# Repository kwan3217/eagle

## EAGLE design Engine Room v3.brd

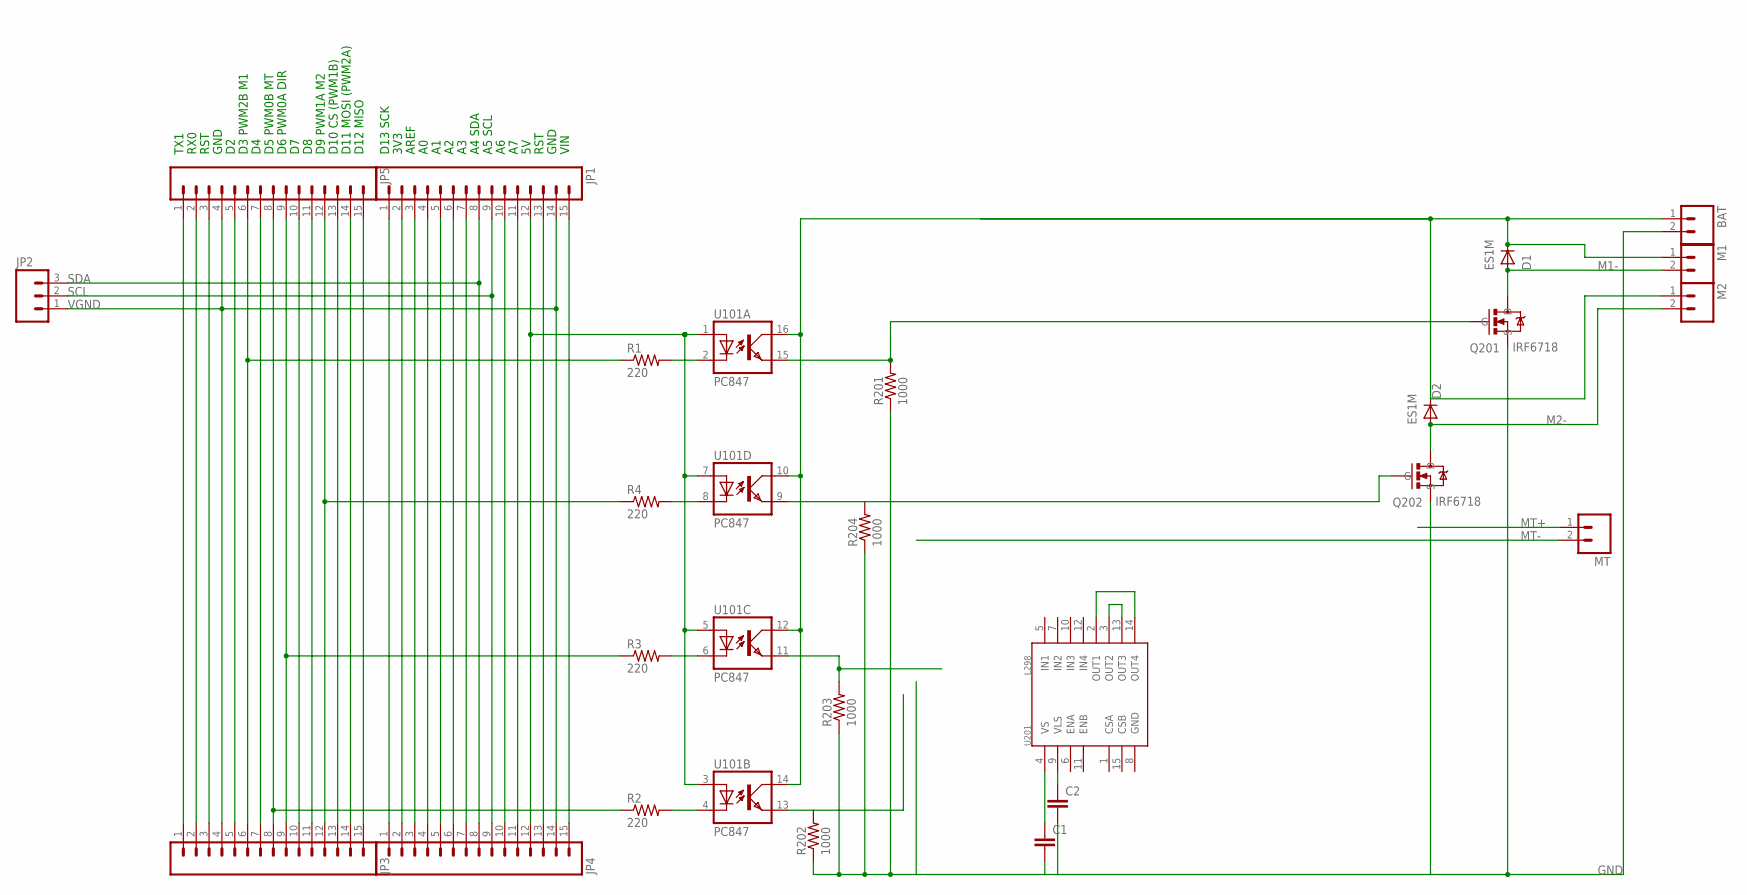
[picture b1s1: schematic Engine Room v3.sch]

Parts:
BAT: M02PTH4; 1X02_XTRA_BIG
C1, C2: CAP0402-CAP; 0402-CAP
D1, D2: ES1M; DO-214AC
JP1, JP5: M15LOCK; 1X15_LOCK
JP2: M03LOCK; 1X03_LOCK
JP3, JP4: M15; 1X15
M1, M2: M02PTH4; 1X02_XTRA_BIG
MT: M02PTH; 1X02
Q201, Q202: IRF6718; DIRECTFET_L6
R1, R2, R3, R4: 220; 0402-RES
R201, R202, R203, R204: 1000; 0402-RES
U101: PC847; DIL16
U201: L298; MULTIWATT15

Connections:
GND: BAT.2, C1.2, C2.2, Q201.S, Q202.S, R201.1, R202.1, R203.1, R204.1
IN1: JP3.6, JP5.6, R1.1
IN2: JP3.12, JP5.12, R4.1
IN3: JP3.8, JP5.8, R2.1
M1-: D1.A, M1.2, Q201.D1 (D), Q201.D2 (D)
M2-: D2.A, M2.2, Q202.D1 (D), Q202.D2 (D)
MT+: MT.1
MT-: MT.2
unnamed: R4.2, U101.8 (C)
unnamed: R3.2, U101.6 (C)
unnamed: R1.2, U101.2 (C)
unnamed: R2.2, U101.4 (C)
unnamed: JP1.15, JP4.15
unnamed: Q201.G, R201.2, U101.15 (EMIT)
unnamed: U201.2 (OUT1), U201.14 (OUT4)
unnamed: Q202.G, R204.2, U101.9 (EMIT)
unnamed: U201.3 (OUT2), U201.13 (OUT3)
unnamed: R203.2, U101.11 (EMIT)
unnamed: JP3.9, JP5.9, R3.1
unnamed: JP3.1, JP5.1
unnamed: JP3.2, JP5.2
unnamed: JP3.3, JP5.3
unnamed: R202.2, U101.13 (EMIT)
unnamed: C2.1, U201.9 (VLS)
unnamed: C1.1, U201.4 (VS)
unnamed: JP3.5, JP5.5
unnamed: JP3.15, JP5.15
unnamed: JP3.14, JP5.14
unnamed: JP3.13, JP5.13
unnamed: JP3.7, JP5.7
unnamed: JP3.10, JP5.10
unnamed: JP3.11, JP5.11
unnamed: JP1.13, JP4.13
unnamed: JP1.11, JP4.11
unnamed: JP1.10, JP4.10
unnamed: JP1.7, JP4.7
unnamed: JP1.6, JP4.6
unnamed: JP1.5, JP4.5
unnamed: JP1.4, JP4.4
unnamed: JP1.3, JP4.3
unnamed: JP1.2, JP4.2
unnamed: JP1.1, JP4.1
SCL: JP1.9, JP2.2, JP4.9
SDA: JP1.8, JP2.3, JP4.8
VCC: JP1.12, JP4.12, U101.1 (A), U101.3 (A), U101.5 (A), U101.7 (A)
VDD: BAT.1, D1.C, D2.C, M1.1, M2.1, U101.10 (COL), U101.12 (COL), U101.14 (COL), U101.16 (COL)
VGND: JP1.14, JP2.1, JP3.4, JP4.14, JP5.4

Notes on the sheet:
VIN
GND
RST
A5 SCL
A4 SDA
AREF
3V3
D13 SCK
D12 MISO
D11 MOSI (PWM2A)
D10 CS (PWM1B)
D9 PWM1A M2
D6 PWM0A DIR
D5 PWM0B MT
D3 PWM2B M1
RX0
TX1

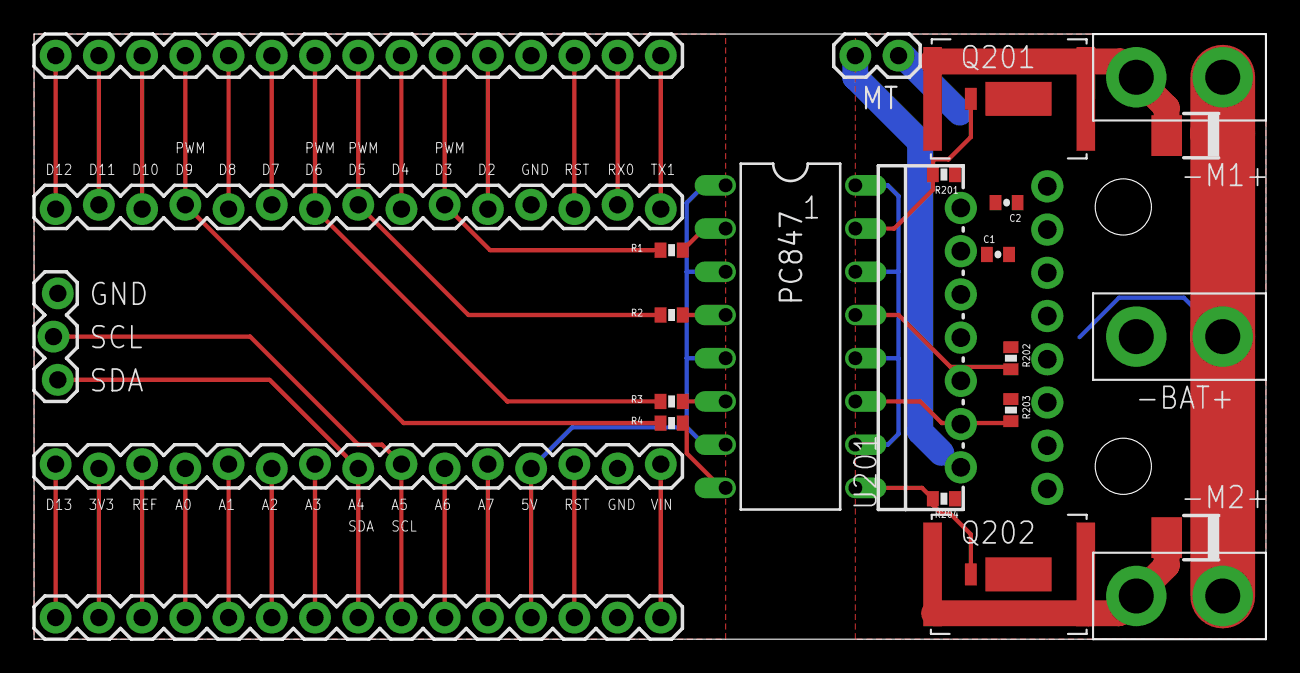
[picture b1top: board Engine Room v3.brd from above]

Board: 2 copper layers, 72.4 x 35.6 mm, 28 parts (1 on the bottom side), 45 nets.

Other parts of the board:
U$1, U$2: STAND-OFF
U$3: KWAN_CIRCLE

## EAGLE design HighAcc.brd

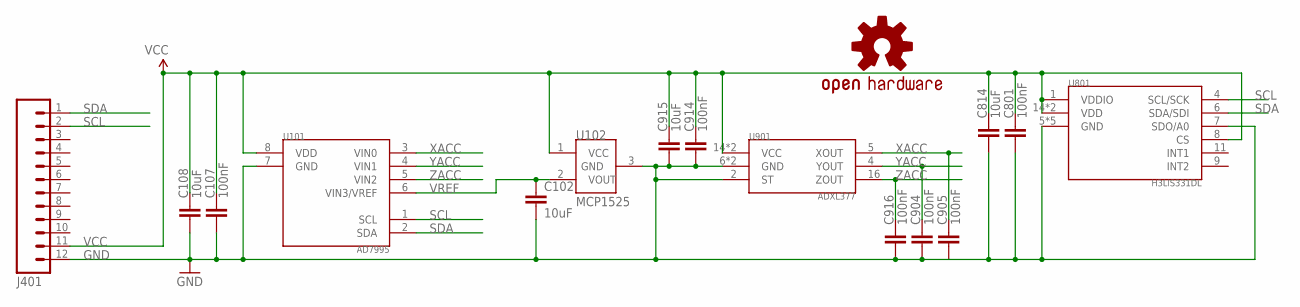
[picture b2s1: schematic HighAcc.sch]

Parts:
C102, C108, C814, C915: 10uF; 0603-CAP; DIGIKEY 445-7486-1-ND
C107, C801, C904, C905, C914, C916: 100nF; 0603-CAP; DIGIKEY 445-1316-1-ND
J401: M12PTH; 1X12; DIGIKEY $NOPART
U101: AD7995; SOT-23-8
U102: MCP1525; SOT-23-3
U801: H3LIS331DL; LLGA16
U901: ADXL377
U$2: OSHW-LOGOS; OSHW-LOGO-S; DIGIKEY $NOPART

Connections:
GND: C102.2, C107.2, C108.2, C801.2, C814.2, C904.2, C905.2, C914.2, C915.2, C916.2, J401.12, U101.7 (GND), U102.3 (GND), U801.5 (GND), U801.7 (SDO/A0), U801.10 (GND), U801.12 (GND), U801.13 (GND), U801.16 (GND), U901.2 (ST), U901.6 (GND), U901.7 (GND)
SCL: J401.2, U101.1 (SCL), U801.4 (SCL/SCK)
SDA: J401.1, U101.2 (SDA), U801.6 (SDA/SDI)
VCC: C107.1, C108.1, C801.1, C814.1, C914.1, C915.1, J401.11, U101.8 (VDD), U102.1 (VCC), U801.1 (VDDIO), U801.8 (CS), U801.14 (VDD), U801.15 (VDD), U901.14 (VCC), U901.15 (VCC)
VREF: C102.1, U101.6 (VIN3/VREF), U102.2 (VOUT)
XACC: C905.1, U101.3 (VIN0), U901.5 (XOUT)
YACC: C904.1, U101.4 (VIN1), U901.4 (YOUT)
ZACC: C916.1, U101.5 (VIN2), U901.16 (ZOUT)

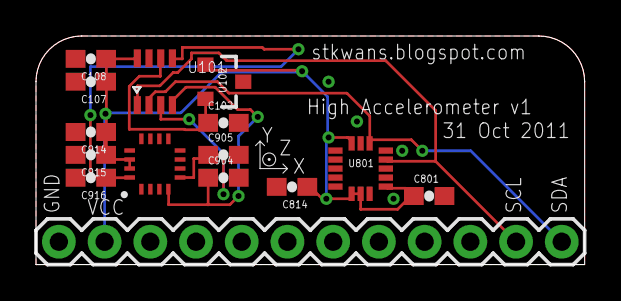
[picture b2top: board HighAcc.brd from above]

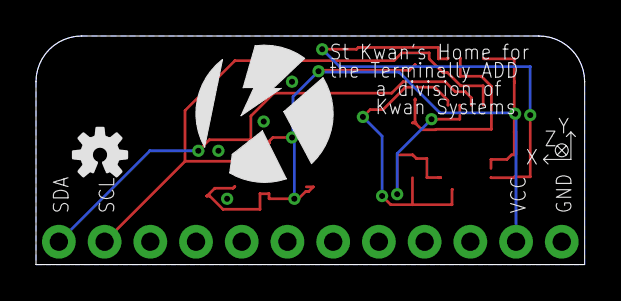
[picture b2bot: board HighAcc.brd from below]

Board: 2 copper layers, 30.5 x 12.7 mm, 17 parts (2 on the bottom side), 8 nets.

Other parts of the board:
U$1: KWAN_CIRCLE

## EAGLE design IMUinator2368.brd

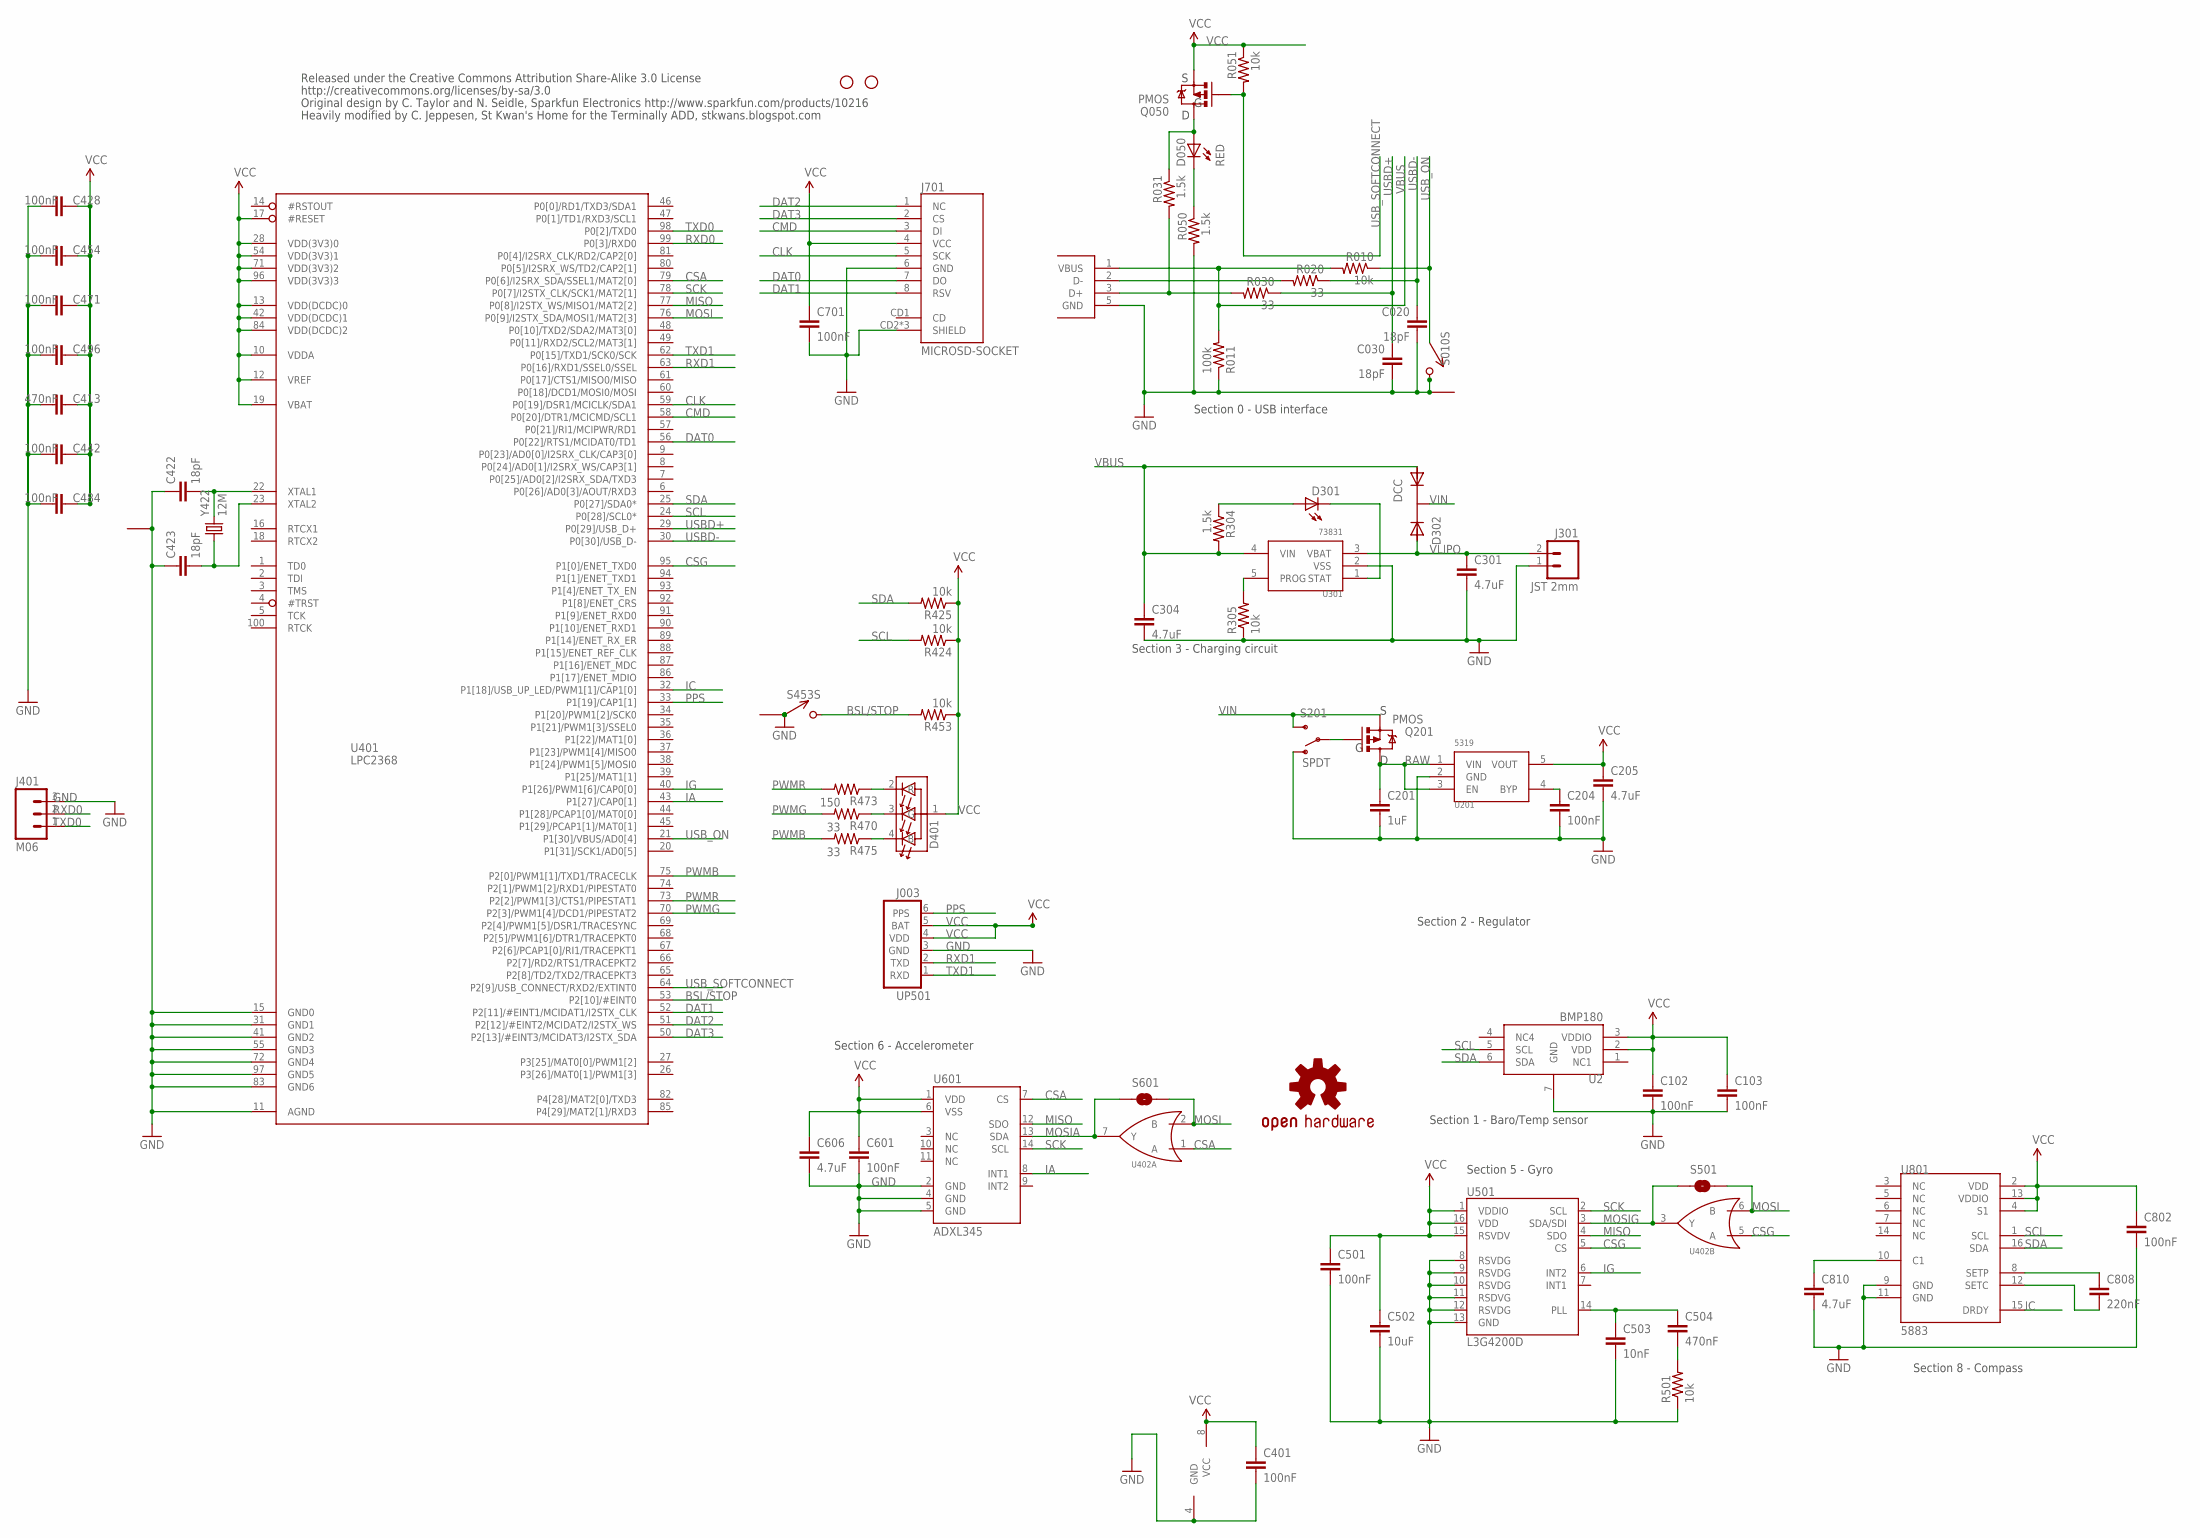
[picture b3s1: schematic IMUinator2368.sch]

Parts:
C020, C030, C422, C423: 18pF; 0402-CAP; DIGIKEY 445-1238-1-ND
C102, C103, C204, C401, C428, C442, C454, C471, C484, C496, C501, C601, C701, C802: 100nF; 0402-CAP; DIGIKEY 445-1268-1-ND
C201: 1uF; 0402-CAP; DIGIKEY 445-1415-1-ND
C205, C301, C304, C606, C810: 4.7uF; 0402-CAP; DIGIKEY 445-7395-1-ND
C413, C504: 470nF; 0402-CAP; DIGIKEY 445-4976-1-ND
C502: 10uF; 0603-CAP; DIGIKEY 445-7486-1-ND
C503: 10nF; 0402-CAP; DIGIKEY 445-4943-1-ND
C808: 220nF; 0402-CAP; DIGIKEY 445-4972-1-ND
D050, D301: RED; LED-0603; DIGIKEY 350-2029-1-ND
D302: DCC; SOT-23-3; DIGIKEY 568-6500-1-ND
D401: RGB; HSMF-C118; DIGIKEY 516-1778-1-ND
J001: USB_MICROB_JST; UB-MC5BR3-SD204-4S; DIGIKEY 455-2562-1-ND
J003: UP501; DIGIKEY $NOPART
J301: JST 2mm; JST-2-SMD; DIGIKEY 455-1749-1-ND
J401: M06; 1X03; DIGIKEY $NOPART
J701: MICROSD-SOCKET; MICROSD-SOCKET-PP; DIGIKEY 101-00581-59-1-ND
JP1, JP2: STAND-OFF; DIGIKEY $NOPART
Q050, Q201: PMOS; SOT23-3; DIGIKEY NTR1P02T1GOSCT-ND
R010, R051, R305, R424, R425, R453, R501: 10k; 0402-RES; DIGIKEY P10.0KLCT-ND
R011: 100k; 0402-RES; DIGIKEY P100KLCT-ND
R020, R030, R475: 33; 0402-RES; DIGIKEY P33.0LCT-ND
R031, R050, R304: 1.5k; 0402-RES; DIGIKEY P1.50KLCT-ND
R470: 33; 0402-RES; DIGIKEY P150LCT-ND
R473: 150; 0402-RES; DIGIKEY P33.0LCT-ND
S010, S453: SPST; B3U-1100P; DIGIKEY SW1021CT-ND
S201: SPDT; AYZ0202; DIGIKEY 401-2013-1-ND
S501, S601: SOLDERJUMPERNO; SJ_2S-NO; DIGIKEY $NOPART
U2: BMP180; DIGIKEY 828-1027-1-ND
U201: 5319; SOT-23-5; DIGIKEY 576-1910-1-ND
U301: 73831; SOT-23-5; DIGIKEY MCP73831T-2ACI/OTCT-ND
U401: LPC2368; LQFP100; DIGIKEY 568-3997-ND
U402: 7432; DCU_8; DIGIKEY 296-13268-1-ND
U501: L3G4200D; LGA16-4X4; DIGIKEY 497-11071-1-ND
U601: ADXL345; LGA14; DIGIKEY ADXL345BCCZ-RL7CT-ND
U801: 5883; 16LPCC; DIGIKEY 342-1082-1-ND
U$3: OSHW-LOGOS; OSHW-LOGO-S; DIGIKEY $NOPART
Y422: 12M; CRYSTAL_SMD; DIGIKEY 887-1316-1-ND

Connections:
BSL/STOP: R453.2, S453.P$2 (2), U401.53 (P2[10]/#EINT0)
CLK: J701.5 (SCK), U401.59 (P0[19]/DSR1/MCICLK/SDA1)
CMD: J701.3 (DI), U401.58 (P0[20]/DTR1/MCICMD/SCL1)
CONN_D+: J001.3 (D+), R030.2, R031.2
CONN_D-: J001.2 (D-), R020.2
CSA: U401.79 (P0[6]/I2SRX_SDA/SSEL1/MAT2[0]), U402.1 (A), U601.7 (CS)
CSG: U401.95 (P1[0]/ENET_TXD0), U402.5 (A), U501.5 (CS)
DAT0: J701.7 (DO), U401.56 (P0[22]/RTS1/MCIDAT0/TD1)
DAT1: J701.8 (RSV), U401.52 (P2[11]/#EINT1/MCIDAT1/I2STX_CLK)
DAT2: J701.1 (NC), U401.51 (P2[12]/#EINT2/MCIDAT2/I2STX_WS)
DAT3: J701.2 (CS), U401.50 (P2[13]/#EINT3/MCIDAT3/I2STX_SDA)
DB: D401.4 (B), R475.1
DG: D401.2 (R), R473.1
DR: D401.3 (G), R470.1
GND: C020.2, C030.2, C102.2, C103.2, C201.2, C204.2, C205.2, C301.2, C304.2, C401.2, C413.2, C422.1, C423.1, C428.2, C442.2, C454.2, C471.2, C484.2, C496.2, C501.2, C502.2, C503.2, C601.2, C606.2, C701.2, C802.2, C810.2, J001.5 (GND), J003.3 (GND), J301.1, J401.3, J701.6 (GND), J701.CD2 (SHIELD), J701.GND1 (SHIELD), J701.GND3 (SHIELD), R011.1, R050.2, R305.1, R501.1, S010.P$2 (2), S010.P$3 (1), S201.1 (O), S453.P$1 (1), S453.P$3 (1), U2.7 (GND), U201.2 (GND), U301.2 (VSS), U401.11 (AGND), U401.15 (GND0), U401.31 (GND1), U401.41 (GND2), U401.55 (GND3), U401.72 (GND4), U401.83 (GND6), U401.97 (GND5), U402.4 (GND), U501.8 (RSVDG), U501.9 (RSVDG), U501.10 (RSVDG), U501.11 (RSDVG), U501.12 (RSVDG), U501.13 (GND), U601.2 (GND), U601.4 (GND), U601.5 (GND), U801.9 (GND), U801.11 (GND), Y422.2 (1)
IA: U401.43 (P1[27]/CAP0[1]), U601.8 (INT1)
IC: U401.32 (P1[18]/USB_UP_LED/PWM1[1]/CAP1[0]), U801.15 (DRDY)
IG: U401.40 (P1[26]/PWM1[6]/CAP0[0]), U501.6 (INT2)
MISO: U401.77 (P0[8]/I2STX_WS/MISO1/MAT2[2]), U501.4 (SDO), U601.12 (SDO)
MOSI: S501.2, S601.2, U401.76 (P0[9]/I2STX_SDA/MOSI1/MAT2[3]), U402.2 (B), U402.6 (B)
MOSIA: S601.1, U402.7 (Y), U601.13 (SDA)
MOSIG: S501.1, U402.3 (Y), U501.3 (SDA/SDI)
unnamed: D301.A, R304.1
unnamed: C503.1, C504.1, U501.14 (PLL)
unnamed: C504.2, R501.2
unnamed: D050.A, Q050.3 (D), R031.1
unnamed: D050.C, R050.1
unnamed: C808.1, U801.8 (SETP)
unnamed: C808.2, U801.12 (SETC)
unnamed: C810.1, U801.10 (C1)
unnamed: C204.1, U201.4 (BYP)
PPS: J003.6 (PPS), U401.33 (P1[19]/CAP1[1])
PWMB: R475.2, U401.75 (P2[0]/PWM1[1]/TXD1/TRACECLK)
PWMG: R470.2, U401.70 (P2[3]/PWM1[4]/DCD1/PIPESTAT2)
PWMR: R473.2, U401.73 (P2[2]/PWM1[3]/CTS1/PIPESTAT1)
PWR_SWITCH: Q201.1 (G), S201.2
RAW: C201.1, Q201.3 (D), U201.1 (VIN), U201.3 (EN)
REG_PROG: R305.2, U301.5 (PROG)
REG_STAT: D301.C, U301.1 (STAT)
RXD0: J401.2, U401.99 (P0[3]/RXD0)
RXD1: J003.2 (TXD), U401.63 (P0[16]/RXD1/SSEL0/SSEL)
SCK: U401.78 (P0[7]/I2STX_CLK/SCK1/MAT2[1]), U501.2 (SCL), U601.14 (SCL)
SCL: R424.2, U2.5 (SCL), U401.24 (P0[28]/SCL0*), U801.1 (SCL)
SDA: R425.2, U2.6 (SDA), U401.25 (P0[27]/SDA0*), U801.16 (SDA)
TXD0: J401.1, U401.98 (P0[2]/TXD0)
TXD1: J003.1 (RXD), U401.62 (P0[15]/TXD1/SCK0/SCK)
USBD+: C030.1, R030.1, U401.29 (P0[29]/USB_D+)
USBD-: C020.1, R020.1, U401.30 (P0[30]/USB_D-)
USB_ON: R010.1, S010.P$1 (1), U401.21 (P1[30]/VBUS/AD0[4])
USB_SOFTCONNECT: Q050.1 (G), R051.2, U401.64 (P2[9]/USB_CONNECT/RXD2/EXTINT0)
VBUS: C304.1, D302.1 (A1), J001.1 (VBUS), R010.2, R011.2, R304.2, U301.4 (VIN)
VCC: C102.1, C103.1, C205.1, C401.1, C413.1, C428.1, C442.1, C454.1, C471.1, C484.1, C496.1, C501.1, C502.1, C601.1, C606.1, C701.1, C802.1, D401.1 (A), J003.4 (VDD), J003.5 (BAT), J701.4 (VCC), Q050.2 (S), R051.1, R424.1, R425.1, R453.1, U2.2 (VDD), U2.3 (VDDIO), U201.5 (VOUT), U401.10 (VDDA), U401.12 (VREF), U401.13 (VDD(DCDC)0), U401.17 (#RESET), U401.19 (VBAT), U401.28 (VDD(3V3)0), U401.42 (VDD(DCDC)1), U401.54 (VDD(3V3)1), U401.71 (VDD(3V3)2), U401.84 (VDD(DCDC)2), U401.96 (VDD(3V3)3), U402.8 (VCC), U501.1 (VDDIO), U501.15 (RSVDV), U501.16 (VDD), U601.1 (VDD), U601.6 (VSS), U801.2 (VDD), U801.4 (S1), U801.13 (VDDIO)
VIN: D302.3 (K), Q201.2 (S), S201.3 (S)
VLIPO: C301.1, D302.2 (A2), J301.2, U301.3 (VBAT)
XTAL1: C422.2, U401.22 (XTAL1), Y422.3 (2)
XTAL2: C423.2, U401.23 (XTAL2), Y422.1

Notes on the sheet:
Section 2 - Regulator
Section 3 - Charging circuit
Section 0 - USB interface
Released under the Creative Commons Attribution Share-Alike 3.0 License
http://creativecommons.org/licenses/by-sa/3.0
Original design by C. Taylor and N. Seidle, Sparkfun Electronics http://www.sparkfun.com/products/10216
Heavily modified by C. Jeppesen, St Kwan's Home for the Terminally ADD, stkwans.blogspot.com
Section 5 - Gyro
Section 6 - Accelerometer
Section 1 - Baro/Temp sensor
Section 8 - Compass

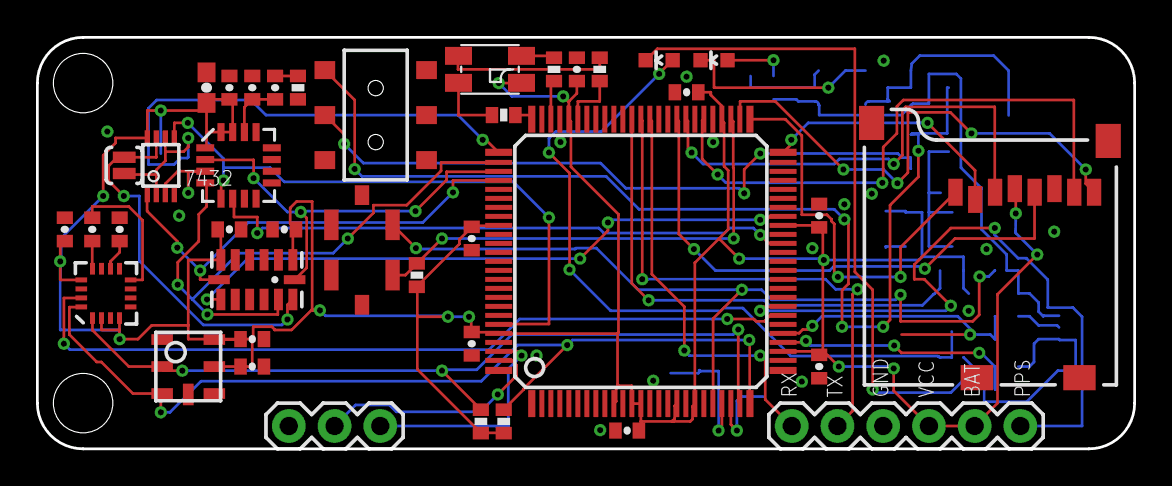
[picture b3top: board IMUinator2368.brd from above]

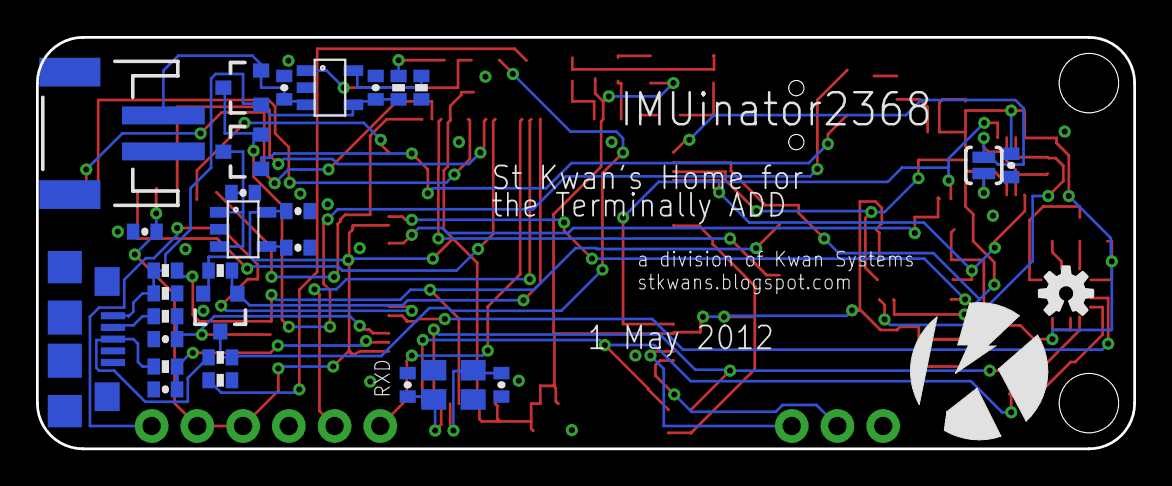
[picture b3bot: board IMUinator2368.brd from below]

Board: 2 copper layers, 61.0 x 22.9 mm, 74 parts (31 on the bottom side), 56 nets.

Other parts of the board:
U$1: KWAN_CIRCLE

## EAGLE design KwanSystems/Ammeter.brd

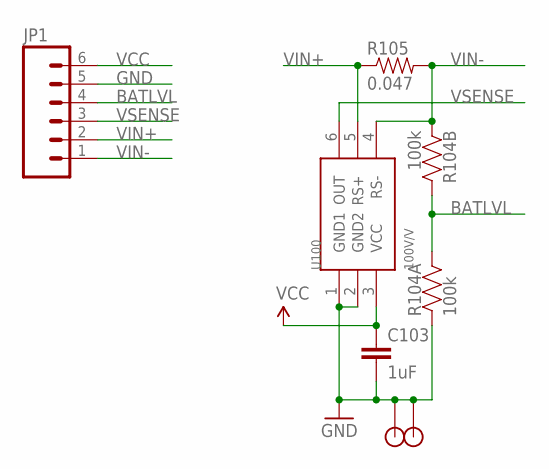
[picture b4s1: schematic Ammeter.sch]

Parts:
C103: 1uF; 0402-CAP; DIGIKEY 445-1415-1-ND
JP1: M06SIP; 1X06
R104: 100k; CRA02
R105: 0.047; 0402-RES; DIGIKEY P.047ATCT-ND
U100: 100V/V; SOT-23-6; DIGIKEY MAX4173HEUT+TCT-ND
U$1, U$2: STANDOFF

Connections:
BATLVL: JP1.4, R104.3 (2), R104.4 (2)
GND: C103.2, JP1.5, R104.1, U100.1 (GND1), U100.2 (GND2), U$1.P$1, U$2.P$1
VCC: C103.1, JP1.6, U100.3 (VCC)
VIN+: JP1.2, R105.1, U100.5 (RS+)
VIN-: JP1.1, R104.2 (1), R105.2, U100.4 (RS-)
VSENSE: JP1.3, U100.6 (OUT)

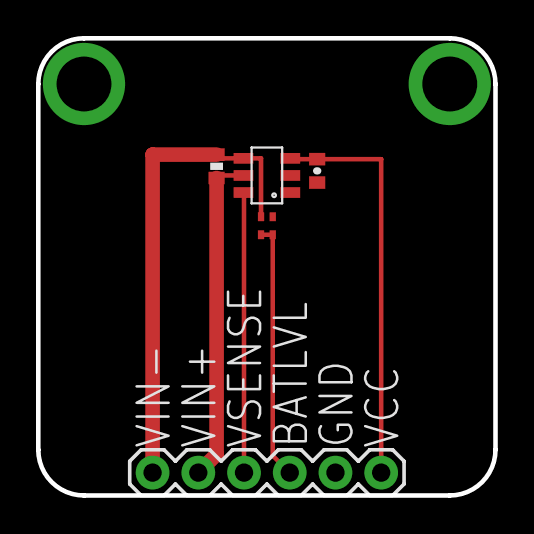
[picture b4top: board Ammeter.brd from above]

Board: 2 copper layers, 25.4 x 25.4 mm, 7 parts (0 on the bottom side), 6 nets.

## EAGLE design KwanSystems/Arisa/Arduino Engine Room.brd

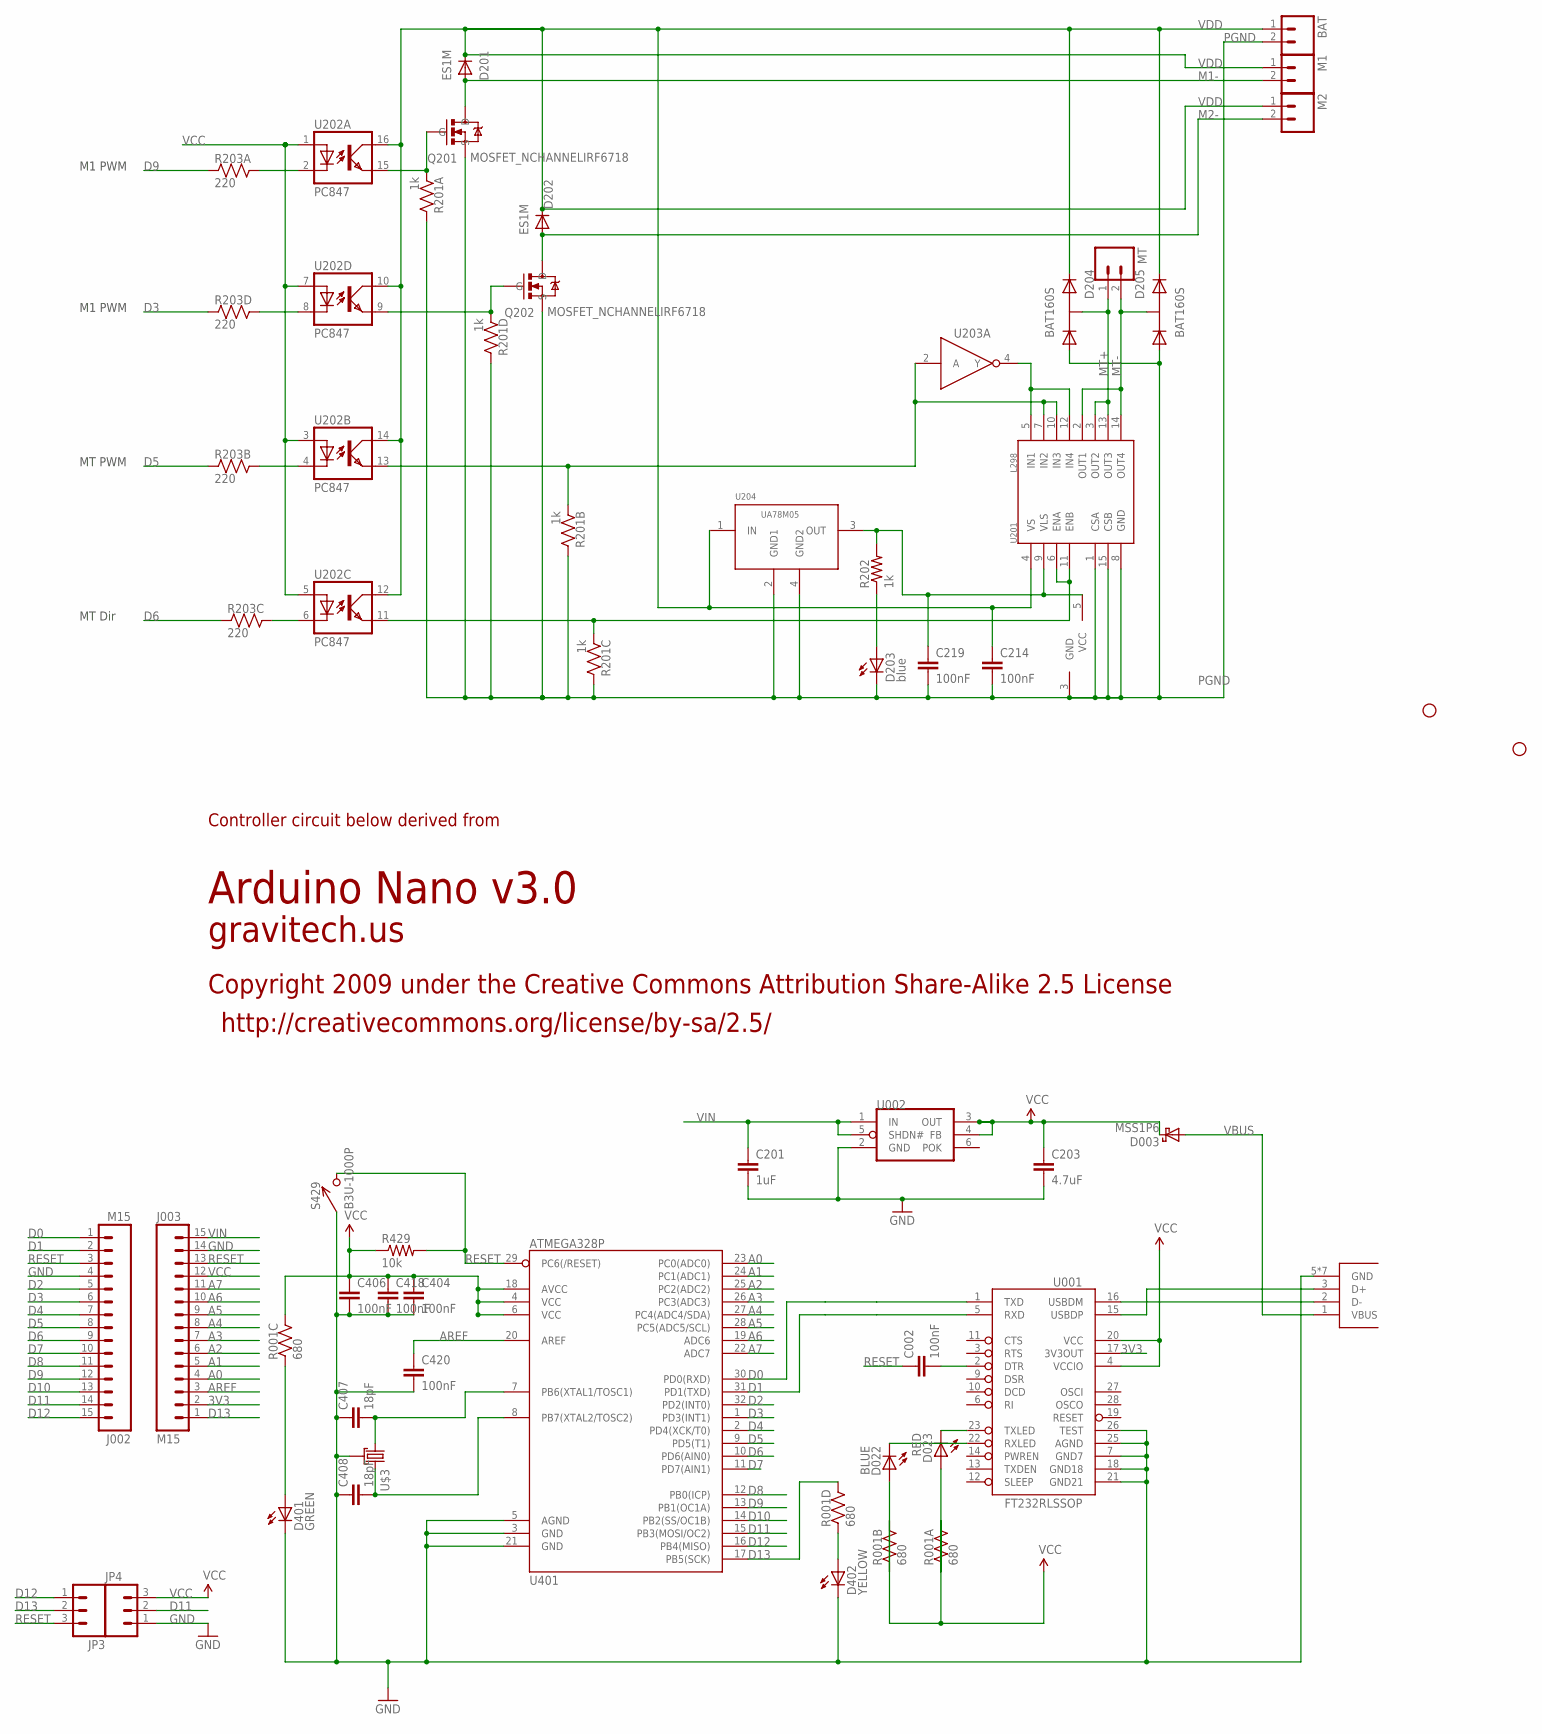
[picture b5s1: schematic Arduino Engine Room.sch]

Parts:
BAT: M02PTH4; 1X02_XTRA_BIG
C002, C404, C406, C418, C420: 100nF; 0402-CAP; DIGIKEY 445-1268-1-ND
C201: 1uF; 0402-CAP; DIGIKEY 445-1415-1-ND
C203: 4.7uF; 0402-CAP; DIGIKEY 445-7395-1-ND
C214, C219: 100nF; 0402-CAP
C407, C408: 18pF; 0402-CAP; DIGIKEY 445-1238-1-ND
D003: MSS1P6; MICROSMP; DIGIKEY MSS1P6-M3/89AGICT-ND
D022: BLUE; LED-0603; DIGIKEY 350-2037-1-ND
D023: RED; LED-0603; DIGIKEY 754-1359-1-ND
D201, D202: ES1M; DO-214AC
D203: blue; LED-0603
D204, D205: BAT160S; SOT-223
D401: GREEN; LED-0603; DIGIKEY 350-2036-1-ND
D402: YELLOW; LED-0603; DIGIKEY 754-1124-1-ND
J001: USB_MICROB_JSTGCT; USB_MICROB_3075; DIGIKEY 455-2562-1-ND
J002, J003: M15; 1X15; DIGIKEY $NOPART
JP1, JP2: STAND-OFF
JP3, JP4: M03PTH; 1X03; DIGIKEY $NOPART
M1, M2: M02PTH4; 1X02_XTRA_BIG
MT: M02PTH; 1X02
Q201, Q202: MOSFET_NCHANNELIRF6718; DIRECTFET_L6
R001: 680; CRA04; DIGIKEY CRA4S8680CT-ND
R201: 1k; CRA04
R202: 1k; 0402-RES
R203: 220; CRA04
R429: 10k; 0402-RES; DIGIKEY P10.0KLCT-ND
S429: B3U-1000P
U001: FT232RLSSOP; SSOP28DB; DIGIKEY 768-1007-1-ND
U002: MAX8881; SOT-23-6; DIGIKEY MAX8881EUT50+TCT-ND
U201: L298; MULTIWATT15
U202: PC847; DIL16
U203: MC74VHC1G04; SOT-23-5
U204: UA78M05; SOT223
U401: ATMEGA328P; TQFP32-08; DIGIKEY ATMEGA328P-15AZCT-ND
U$3: CX2520; CRYSTAL_SMD_2MM_2_5MM

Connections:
3V3: J003.2, U001.17 (3V3OUT)
A0: J003.4, U401.23 (PC0(ADC0))
A1: J003.5, U401.24 (PC1(ADC1))
A2: J003.6, U401.25 (PC2(ADC2))
A3: J003.7, U401.26 (PC3(ADC3))
A4: J003.8, U401.27 (PC4(ADC4/SDA))
A5: J003.9, U401.28 (PC5(ADC5/SCL))
A6: J003.10, U401.19 (ADC6)
A7: J003.11, U401.22 (ADC7)
AREF: C420.1, J003.3, U401.20 (AREF)
D0: J002.1, U001.1 (TXD), U401.30 (PD0(RXD))
D1: J002.2, U001.5 (RXD), U401.31 (PD1(TXD))
D2: J002.5, U401.32 (PD2(INT0))
D3: J002.6, R203.4 (1), U401.1 (PD3(INT1))
D3_ISO: R203.5 (2), U202.8 (C)
D4: J002.7, U401.2 (PD4(XCK/T0))
D5: J002.8, R203.2 (1), U401.9 (PD5(T1))
D5_ISO: R203.7 (2), U202.4 (C)
D6: J002.9, R203.3 (1), U401.10 (PD6(AIN0))
D6_ISO: R203.6 (2), U202.6 (C)
D7: J002.10, U401.11 (PD7(AIN1))
D8: J002.11, U401.12 (PB0(ICP))
D9: J002.12, R203.1, U401.13 (PB1(OC1A))
D9_ISO: R203.8 (2), U202.2 (C)
D10: J002.13, U401.14 (PB2(SS/OC1B))
D11: J002.14, JP4.2, U401.15 (PB3(MOSI/OC2))
D12: J002.15, JP3.1, U401.16 (PB4(MISO))
D13: J003.1, JP3.2, R001.5 (2), U401.17 (PB5(SCK))
DTR#: C002.2, U001.2 (DTR)
GND: C201.2, C203.2, C404.2, C406.2, C407.1, C408.1, C418.2, C420.2, D401.C, D402.C, J001.5 (GND), J001.P$1 (GND), J001.P$2 (GND), J001.P$3 (GND), J001.P$4 (GND), J001.P$8 (GND), J001.P$10 (GND), J002.4, J003.14, JP4.1, S429.P$1 (1), U001.7 (GND7), U001.18 (GND18), U001.21 (GND21), U001.25 (AGND), U001.26 (TEST), U002.2 (GND), U401.3 (GND), U401.5 (AGND), U401.21 (GND), U$3.2 (GND), U$3.4 (GND)
M1-: D201.A, M1.2, Q201.D1 (D), Q201.D2 (D)
M2-: D202.A, M2.2, Q202.D1 (D), Q202.D2 (D)
MT+: D204.4 (K1A2), MT.1, U201.3 (OUT2), U201.13 (OUT3)
MT-: D205.4 (K1A2), MT.2, U201.2 (OUT1), U201.14 (OUT4)
unnamed: D203.A, R202.1
unnamed: U201.5 (IN1), U201.12 (IN4), U203.4 (Y)
unnamed: C407.2, U401.7 (PB6(XTAL1/TOSC1)), U$3.1
unnamed: C408.2, U401.8 (PB7(XTAL2/TOSC2)), U$3.3 (2)
unnamed: J001.3 (D+), U001.15 (USBDP)
unnamed: J001.2 (D-), U001.16 (USBDM)
unnamed: D401.A, R001.3 (1)
unnamed: D402.A, R001.4 (1)
unnamed: D022.A, R001.2 (1)
unnamed: C219.1, R202.2, U201.9 (VLS), U203.5 (VCC), U204.3 (OUT)
unnamed: D023.A, R001.1
unnamed: R201.3 (1), U201.6 (ENA), U201.11 (ENB), U202.11 (EMIT)
unnamed: Q201.G, R201.1, U202.15 (EMIT)
unnamed: Q202.G, R201.4 (1), U202.9 (EMIT)
unnamed: R201.2 (1), U201.7 (IN2), U201.10 (IN3), U202.13 (EMIT), U203.2 (A)
PGND: BAT.2, C214.2, C219.2, D203.C, D204.1 (A1), D205.1 (A1), Q201.S, Q202.S, R201.5 (2), R201.6 (2), R201.7 (2), R201.8 (2), U201.1 (CSA), U201.8 (GND), U201.15 (CSB), U203.3 (GND), U204.2 (GND1), U204.4 (GND2)
RESET: C002.1, J002.3, J003.13, JP3.3, R429.2, S429.P$2 (2), U401.29 (PC6(/RESET))
RXLED1: D022.C, U001.22 (RXLED)
TXLED1: D023.C, U001.23 (TXLED)
VBUS: D003.A, J001.1 (VBUS)
VCC: C203.1, C404.1, C406.1, C418.1, D003.K, J003.12, JP4.3, R001.6 (2), R001.7 (2), R001.8 (2), R429.1, U001.4 (VCCIO), U001.20 (VCC), U002.3 (OUT), U002.4 (FB), U202.1 (A), U202.3 (A), U202.5 (A), U202.7 (A), U401.4 (VCC), U401.6 (VCC), U401.18 (AVCC)
VDD: BAT.1, C214.1, D201.C, D202.C, D204.3 (K2), D205.3 (K2), M1.1, M2.1, U201.4 (VS), U202.10 (COL), U202.12 (COL), U202.14 (COL), U202.16 (COL), U204.1 (IN)
VIN: C201.1, J003.15, U002.1 (IN), U002.5 (SHDN#)

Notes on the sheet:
Arduino Nano v3.0
Copyright 2009 under the Creative Commons Attribution Share-Alike 2.5 License
http://creativecommons.org/license/by-sa/2.5/
Controller circuit below derived from
gravitech.us
M1 PWM
MT Dir
MT PWM

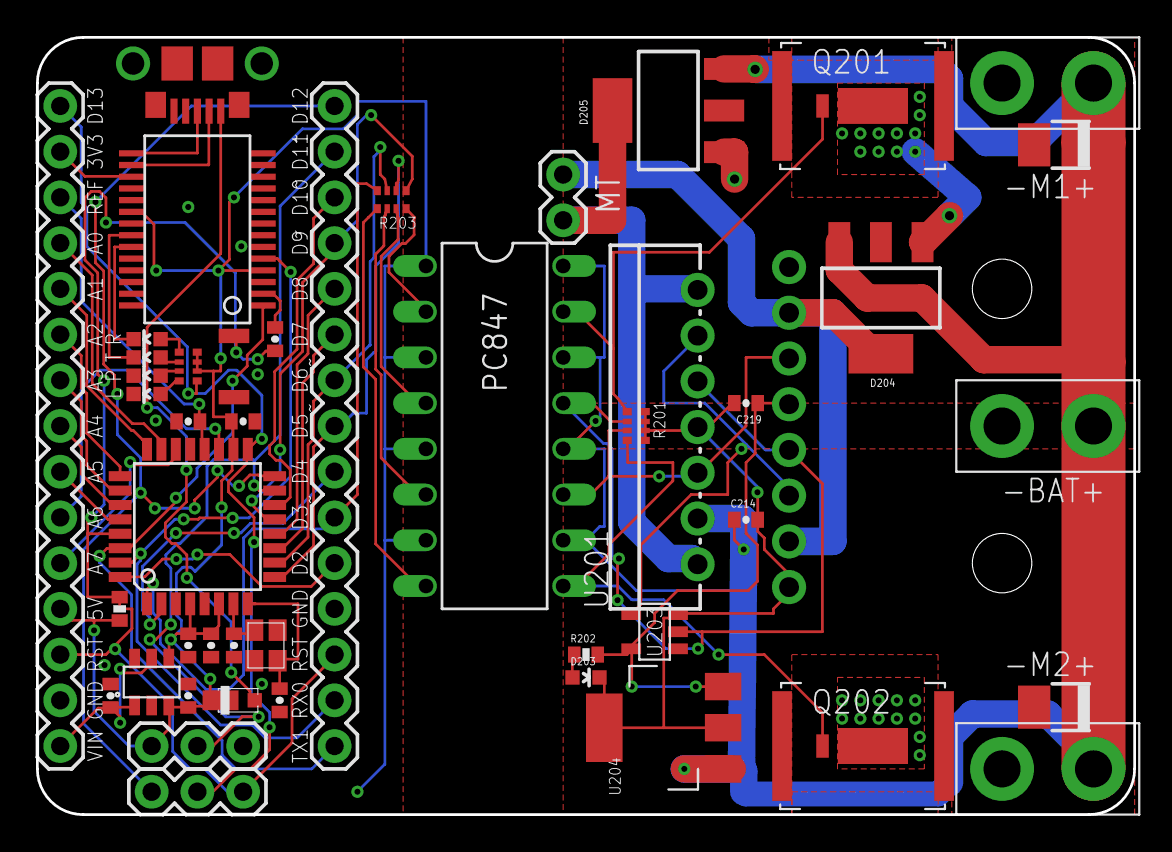
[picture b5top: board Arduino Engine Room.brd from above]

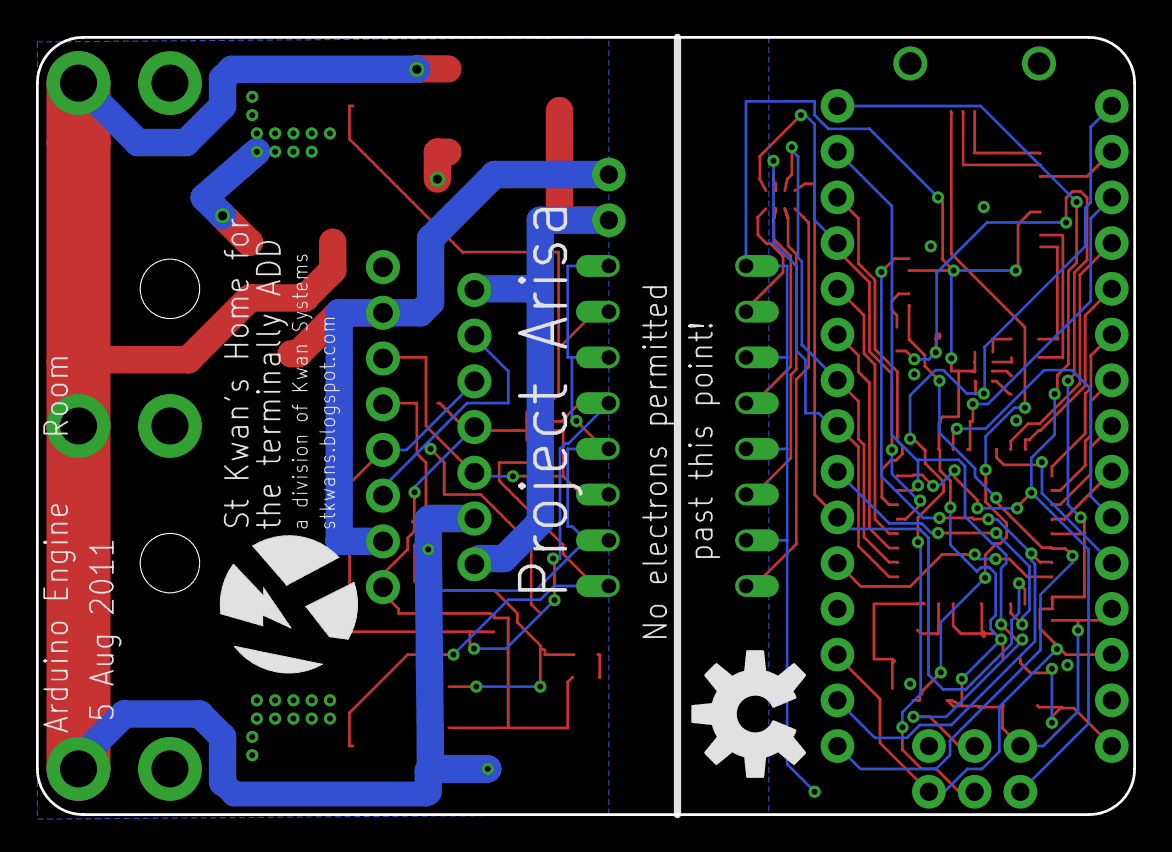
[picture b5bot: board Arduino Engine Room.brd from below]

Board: 2 copper layers, 61.0 x 43.2 mm, 50 parts (2 on the bottom side), 57 nets.

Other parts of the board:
U$1: KWAN_CIRCLE
U$2: OSHW-LOGO-L

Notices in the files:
parts and their libraries:
SparkFun-Passives: Licensing: CC v3.0 Share-Alike You are welcome to use this library for commercial purposes.
